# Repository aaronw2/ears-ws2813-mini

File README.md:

# ears-ws2813-mini
New flex board LED project using ws2812-minis instead of sk6812-3535s. Hopefully this will be less sensitive to heat.

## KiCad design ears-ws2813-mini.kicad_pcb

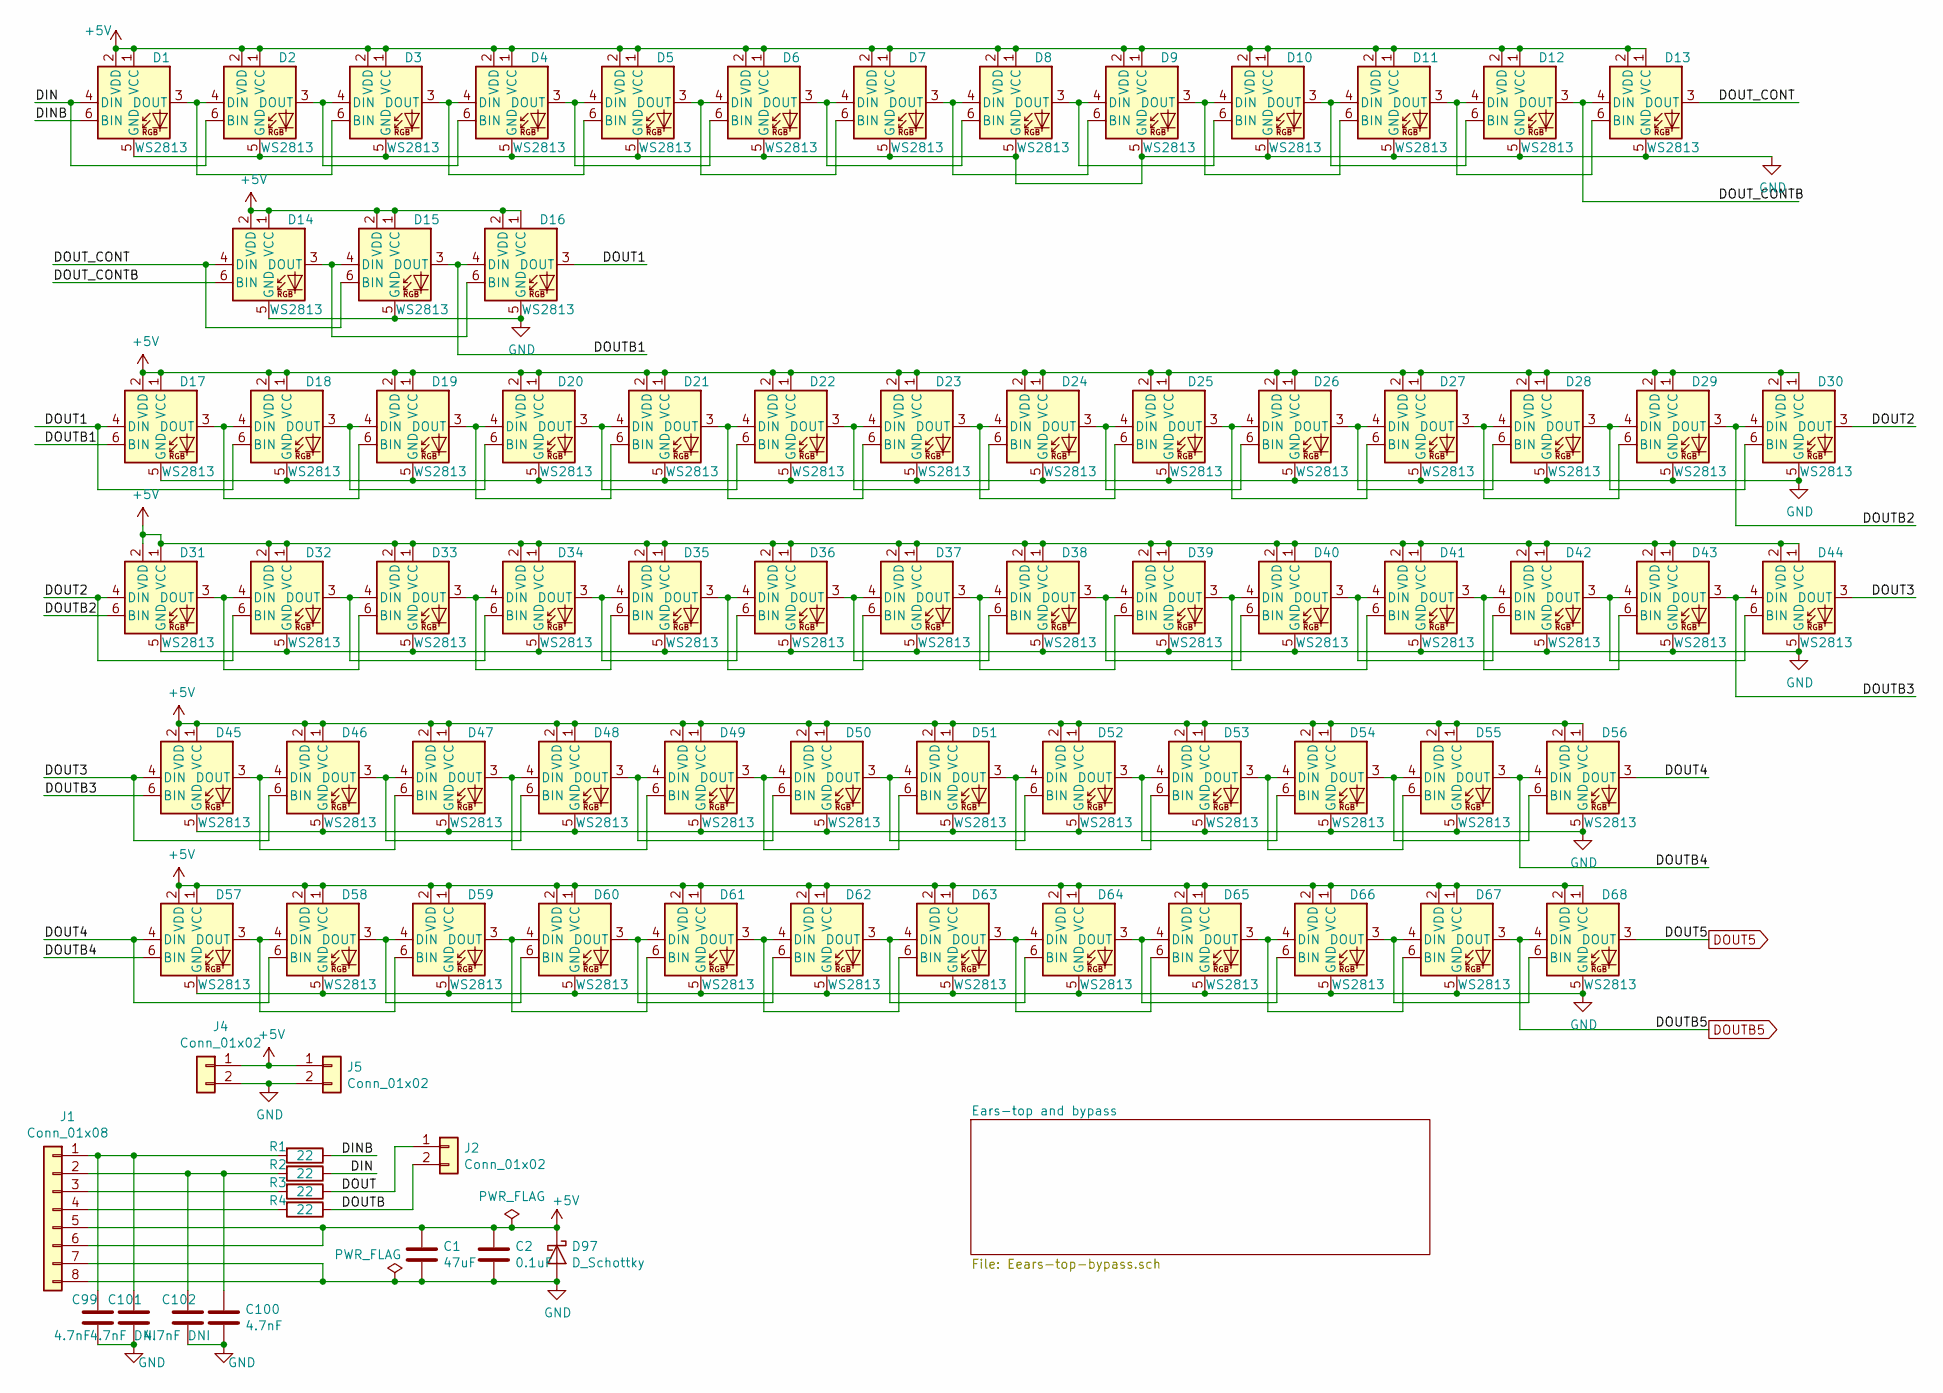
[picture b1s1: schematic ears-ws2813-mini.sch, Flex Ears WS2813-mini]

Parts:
C1: 47uF; C_1210_3225Metric
C2: 0.1uF; C_0603_1608Metric; MPN CL10B104KO8WPNC
C99, C100: 4.7nF; C_0603_1608Metric; MPN CL10B104KO8WPNC
C101, C102: 4.7nF DNI; C_0603_1608Metric; MPN CL10B104KO8WPNC
D1, D2, D3, D4, D5, D6, D7, D8, D9, D10, D11, D12, D13, D14, D15, D16, D17, D18, D19, D20, D21, D22, D23, D24, D25, D26, D27, D28, D29, D30, D31, D32, D33, D34, D35, D36, D37, D38, D39, D40, D41, D42, D43, D44, D45, D46, D47, D48, D49, D50, D51, D52, D53, D54, D55, D56, D57, D58, D59, D60, D61, D62, D63, D64, D65, D66, D67, D68: WS2813; LED_WS2813-MINI-2; MPN WS2813B-Mini
D97: D_Schottky; D_2010_5025Metric; MPN ACDBAT3100-HF
J1: Conn_01x08; PinHeader_1x08_P2.54mm_Vertical
J2, J4, J5: Conn_01x02; PinHeader_1x02_P2.54mm_Vertical
R1, R2, R3, R4: 22; R_0603_1608Metric

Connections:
+5V: C1.1, C2.1, D1.1 (VCC), D1.2 (VDD), D2.1 (VCC), D2.2 (VDD), D3.1 (VCC), D3.2 (VDD), D4.1 (VCC), D4.2 (VDD), D5.1 (VCC), D5.2 (VDD), D6.1 (VCC), D6.2 (VDD), D7.1 (VCC), D7.2 (VDD), D8.1 (VCC), D8.2 (VDD), D9.1 (VCC), D9.2 (VDD), D10.1 (VCC), D10.2 (VDD), D11.1 (VCC), D11.2 (VDD), D12.1 (VCC), D12.2 (VDD), D13.1 (VCC), D13.2 (VDD), D14.1 (VCC), D14.2 (VDD), D15.1 (VCC), D15.2 (VDD), D16.1 (VCC), D16.2 (VDD), D17.1 (VCC), D17.2 (VDD), D18.1 (VCC), D18.2 (VDD), D19.1 (VCC), D19.2 (VDD), D20.1 (VCC), D20.2 (VDD), D21.1 (VCC), D21.2 (VDD), D22.1 (VCC), D22.2 (VDD), D23.1 (VCC), D23.2 (VDD), D24.1 (VCC), D24.2 (VDD), D25.1 (VCC), D25.2 (VDD), D26.1 (VCC), D26.2 (VDD), D27.1 (VCC), D27.2 (VDD), D28.1 (VCC), D28.2 (VDD), D29.1 (VCC), D29.2 (VDD), D30.1 (VCC), D30.2 (VDD), D31.1 (VCC), D31.2 (VDD), D32.1 (VCC), D32.2 (VDD), D33.1 (VCC), D33.2 (VDD), D34.1 (VCC), D34.2 (VDD), D35.1 (VCC), D35.2 (VDD), D36.1 (VCC), D36.2 (VDD), D37.1 (VCC), D37.2 (VDD), D38.1 (VCC), D38.2 (VDD), D39.1 (VCC), D39.2 (VDD), D40.1 (VCC), D40.2 (VDD), D41.1 (VCC), D41.2 (VDD), D42.1 (VCC), D42.2 (VDD), D43.1 (VCC), D43.2 (VDD), D44.1 (VCC), D44.2 (VDD), D45.1 (VCC), D45.2 (VDD), D46.1 (VCC), D46.2 (VDD), D47.1 (VCC), D47.2 (VDD), D48.1 (VCC), D48.2 (VDD), D49.1 (VCC), D49.2 (VDD), D50.1 (VCC), D50.2 (VDD), D51.1 (VCC), D51.2 (VDD), D52.1 (VCC), D52.2 (VDD), D53.1 (VCC), D53.2 (VDD), D54.1 (VCC), D54.2 (VDD), D55.1 (VCC), D55.2 (VDD), D56.1 (VCC), D56.2 (VDD), D57.1 (VCC), D57.2 (VDD), D58.1 (VCC), D58.2 (VDD), D59.1 (VCC), D59.2 (VDD), D60.1 (VCC), D60.2 (VDD), D61.1 (VCC), D61.2 (VDD), D62.1 (VCC), D62.2 (VDD), D63.1 (VCC), D63.2 (VDD), D64.1 (VCC), D64.2 (VDD), D65.1 (VCC), D65.2 (VDD), D66.1 (VCC), D66.2 (VDD), D67.1 (VCC), D67.2 (VDD), D68.1 (VCC), D68.2 (VDD), D97.1 (K), J1.5, J1.6, J4.1, J5.1; also elsewhere on the board
/DIN: D1.4 (DIN), D2.6 (BIN), R2.1
/DINB: D1.6 (BIN), R1.1
/DOUT: J2.1, R3.1
/DOUT1: D16.3 (DOUT), D17.4 (DIN), D18.6 (BIN)
/DOUT2: D30.3 (DOUT), D31.4 (DIN), D32.6 (BIN)
/DOUT3: D44.3 (DOUT), D45.4 (DIN), D46.6 (BIN)
/DOUT4: D56.3 (DOUT), D57.4 (DIN), D58.6 (BIN)
/DOUTB: J2.2, R4.1
/DOUTB1: D15.3 (DOUT), D16.4 (DIN), D17.6 (BIN)
/DOUTB2: D29.3 (DOUT), D30.4 (DIN), D31.6 (BIN)
/DOUTB3: D43.3 (DOUT), D44.4 (DIN), D45.6 (BIN)
/DOUTB4: D55.3 (DOUT), D56.4 (DIN), D57.6 (BIN)
/DOUT_CONT: D13.3 (DOUT), D14.4 (DIN), D15.6 (BIN)
/DOUT_CONTB: D12.3 (DOUT), D13.4 (DIN), D14.6 (BIN)
DOUT5: D68.3 (DOUT); also elsewhere on the board
DOUTB5: D67.3 (DOUT), D68.4 (DIN); also elsewhere on the board
GND: C1.2, C2.2, C99.2, C100.2, C101.2, C102.2, D1.5 (GND), D2.5 (GND), D3.5 (GND), D4.5 (GND), D5.5 (GND), D6.5 (GND), D7.5 (GND), D8.5 (GND), D9.5 (GND), D10.5 (GND), D11.5 (GND), D12.5 (GND), D13.5 (GND), D14.5 (GND), D15.5 (GND), D16.5 (GND), D17.5 (GND), D18.5 (GND), D19.5 (GND), D20.5 (GND), D21.5 (GND), D22.5 (GND), D23.5 (GND), D24.5 (GND), D25.5 (GND), D26.5 (GND), D27.5 (GND), D28.5 (GND), D29.5 (GND), D30.5 (GND), D31.5 (GND), D32.5 (GND), D33.5 (GND), D34.5 (GND), D35.5 (GND), D36.5 (GND), D37.5 (GND), D38.5 (GND), D39.5 (GND), D40.5 (GND), D41.5 (GND), D42.5 (GND), D43.5 (GND), D44.5 (GND), D45.5 (GND), D46.5 (GND), D47.5 (GND), D48.5 (GND), D49.5 (GND), D50.5 (GND), D51.5 (GND), D52.5 (GND), D53.5 (GND), D54.5 (GND), D55.5 (GND), D56.5 (GND), D57.5 (GND), D58.5 (GND), D59.5 (GND), D60.5 (GND), D61.5 (GND), D62.5 (GND), D63.5 (GND), D64.5 (GND), D65.5 (GND), D66.5 (GND), D67.5 (GND), D68.5 (GND), D97.2 (A), J1.7, J1.8, J4.2, J5.2; also elsewhere on the board
unnamed: C100.1, C102.1, J1.2, R2.2
unnamed: C99.1, C101.1, J1.1, R1.2
unnamed: D1.3 (DOUT), D2.4 (DIN), D3.6 (BIN)
unnamed: D2.3 (DOUT), D3.4 (DIN), D4.6 (BIN)
unnamed: D3.3 (DOUT), D4.4 (DIN), D5.6 (BIN)
unnamed: D4.3 (DOUT), D5.4 (DIN), D6.6 (BIN)
unnamed: D5.3 (DOUT), D6.4 (DIN), D7.6 (BIN)
unnamed: D6.3 (DOUT), D7.4 (DIN), D8.6 (BIN)
unnamed: D7.3 (DOUT), D8.4 (DIN), D9.6 (BIN)
unnamed: D10.3 (DOUT), D11.4 (DIN), D12.6 (BIN)
unnamed: D9.3 (DOUT), D10.4 (DIN), D11.6 (BIN)
unnamed: D8.3 (DOUT), D9.4 (DIN), D10.6 (BIN)
unnamed: D11.3 (DOUT), D12.4 (DIN), D13.6 (BIN)
unnamed: D14.3 (DOUT), D15.4 (DIN), D16.6 (BIN)
unnamed: D17.3 (DOUT), D18.4 (DIN), D19.6 (BIN)
unnamed: D18.3 (DOUT), D19.4 (DIN), D20.6 (BIN)
unnamed: D19.3 (DOUT), D20.4 (DIN), D21.6 (BIN)
unnamed: D20.3 (DOUT), D21.4 (DIN), D22.6 (BIN)
unnamed: D21.3 (DOUT), D22.4 (DIN), D23.6 (BIN)
unnamed: D22.3 (DOUT), D23.4 (DIN), D24.6 (BIN)
unnamed: D23.3 (DOUT), D24.4 (DIN), D25.6 (BIN)
unnamed: D24.3 (DOUT), D25.4 (DIN), D26.6 (BIN)
unnamed: D25.3 (DOUT), D26.4 (DIN), D27.6 (BIN)
unnamed: D26.3 (DOUT), D27.4 (DIN), D28.6 (BIN)
unnamed: D27.3 (DOUT), D28.4 (DIN), D29.6 (BIN)
unnamed: D28.3 (DOUT), D29.4 (DIN), D30.6 (BIN)
unnamed: D31.3 (DOUT), D32.4 (DIN), D33.6 (BIN)
unnamed: D32.3 (DOUT), D33.4 (DIN), D34.6 (BIN)
unnamed: D33.3 (DOUT), D34.4 (DIN), D35.6 (BIN)
unnamed: D34.3 (DOUT), D35.4 (DIN), D36.6 (BIN)
unnamed: D35.3 (DOUT), D36.4 (DIN), D37.6 (BIN)
unnamed: D36.3 (DOUT), D37.4 (DIN), D38.6 (BIN)
unnamed: D37.3 (DOUT), D38.4 (DIN), D39.6 (BIN)
unnamed: D38.3 (DOUT), D39.4 (DIN), D40.6 (BIN)
unnamed: D39.3 (DOUT), D40.4 (DIN), D41.6 (BIN)
unnamed: D40.3 (DOUT), D41.4 (DIN), D42.6 (BIN)
unnamed: D41.3 (DOUT), D42.4 (DIN), D43.6 (BIN)
unnamed: D42.3 (DOUT), D43.4 (DIN), D44.6 (BIN)
unnamed: D45.3 (DOUT), D46.4 (DIN), D47.6 (BIN)
unnamed: D46.3 (DOUT), D47.4 (DIN), D48.6 (BIN)
unnamed: D47.3 (DOUT), D48.4 (DIN), D49.6 (BIN)
unnamed: D48.3 (DOUT), D49.4 (DIN), D50.6 (BIN)
unnamed: D49.3 (DOUT), D50.4 (DIN), D51.6 (BIN)
unnamed: D50.3 (DOUT), D51.4 (DIN), D52.6 (BIN)
unnamed: D51.3 (DOUT), D52.4 (DIN), D53.6 (BIN)
unnamed: D52.3 (DOUT), D53.4 (DIN), D54.6 (BIN)
unnamed: D53.3 (DOUT), D54.4 (DIN), D55.6 (BIN)
unnamed: D54.3 (DOUT), D55.4 (DIN), D56.6 (BIN)
unnamed: D57.3 (DOUT), D58.4 (DIN), D59.6 (BIN)
unnamed: D58.3 (DOUT), D59.4 (DIN), D60.6 (BIN)
unnamed: D59.3 (DOUT), D60.4 (DIN), D61.6 (BIN)
unnamed: D60.3 (DOUT), D61.4 (DIN), D62.6 (BIN)
unnamed: D61.3 (DOUT), D62.4 (DIN), D63.6 (BIN)
unnamed: D62.3 (DOUT), D63.4 (DIN), D64.6 (BIN)
unnamed: D63.3 (DOUT), D64.4 (DIN), D65.6 (BIN)
unnamed: D64.3 (DOUT), D65.4 (DIN), D66.6 (BIN)
unnamed: D65.3 (DOUT), D66.4 (DIN), D67.6 (BIN)
unnamed: D66.3 (DOUT), D67.4 (DIN), D68.6 (BIN)
unnamed: J1.3, R3.2
unnamed: J1.4, R4.2

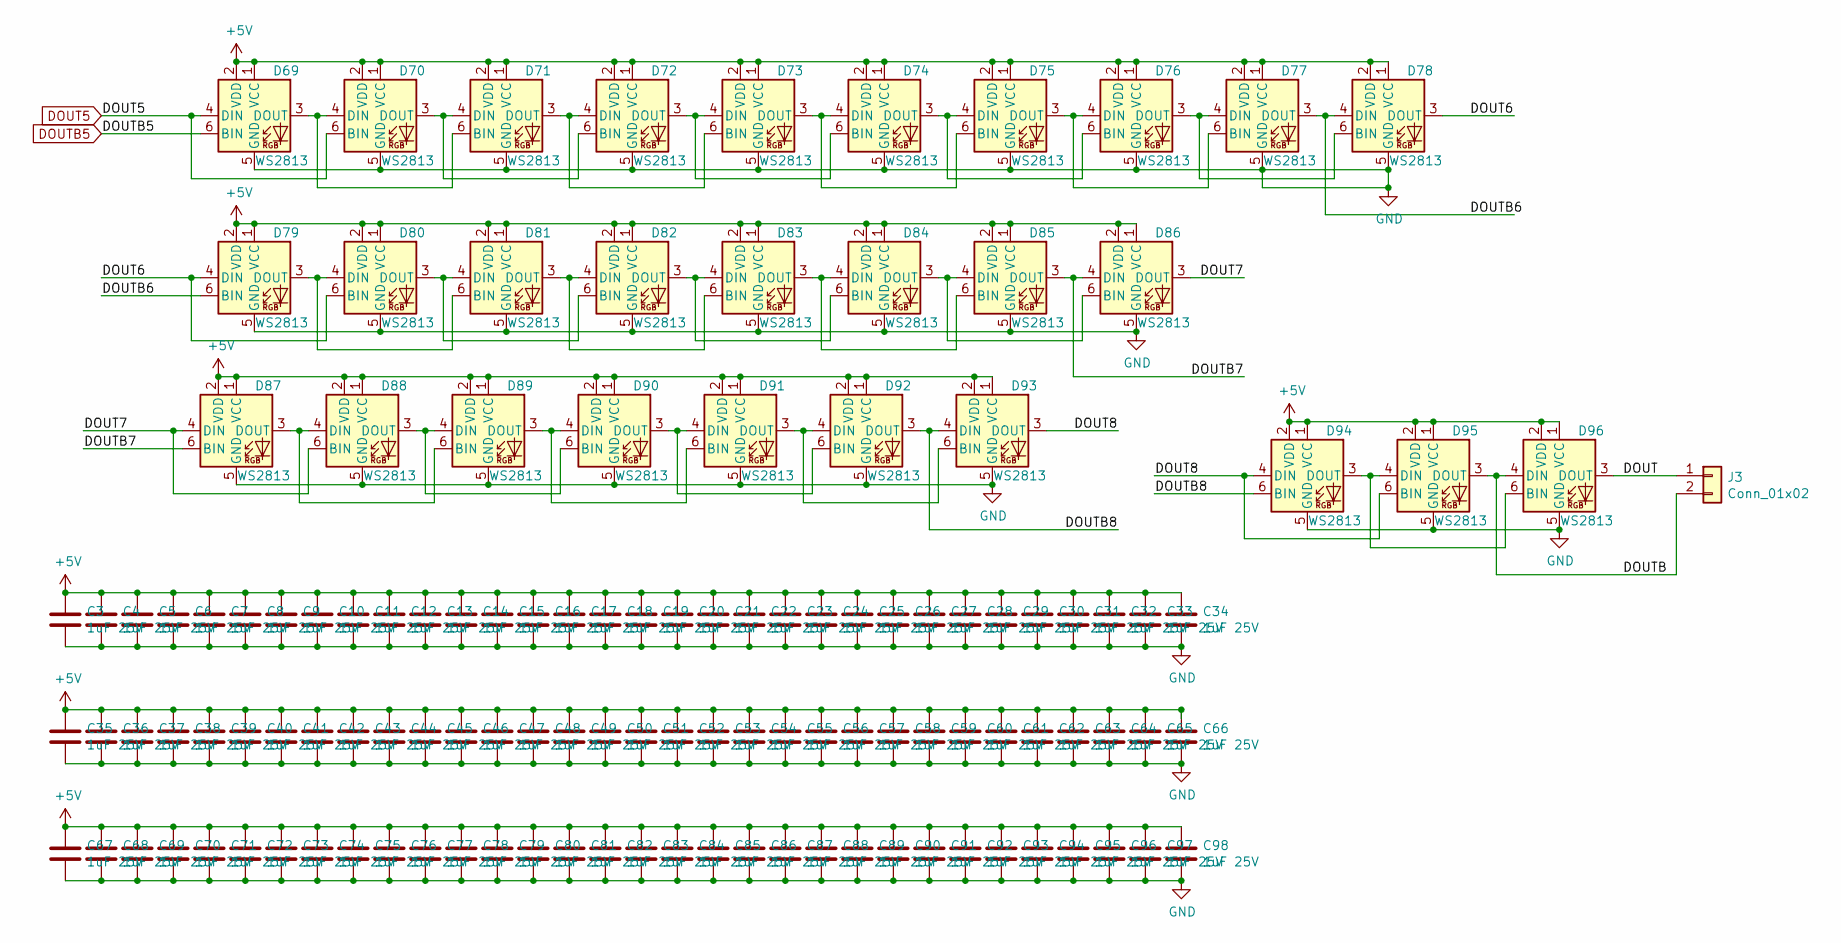
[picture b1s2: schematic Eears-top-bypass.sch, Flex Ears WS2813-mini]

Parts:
C3, C4, C5, C6, C7, C8, C9, C10, C11, C12, C13, C14, C15, C16, C17, C18, C19, C20, C21, C22, C23, C24, C25, C26, C27, C28, C29, C30, C31, C32, C33, C34, C35, C36, C37, C38, C39, C40, C41, C42, C43, C44, C45, C46, C47, C48, C49, C50, C51, C52, C53, C54, C55, C56, C57, C58, C59, C60, C61, C62, C63, C64, C65, C66, C67, C68, C69, C70, C71, C72, C73, C74, C75, C76, C77, C78, C79, C80, C81, C82, C83, C84, C85, C86, C87, C88, C89, C90, C91, C92, C93, C94, C95, C96, C97, C98: 1uF 25V; C_0603_1608Metric; MPN CL10B105KA8NNNC
D69, D70, D71, D72, D73, D74, D75, D76, D77, D78, D79, D80, D81, D82, D83, D84, D85, D86, D87, D88, D89, D90, D91, D92, D93, D94, D95, D96: WS2813; LED_WS2813-MINI; MPN WS2813B-Mini
J3: Conn_01x02; PinHeader_1x02_P2.54mm_Vertical

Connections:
+5V: C3.1, C4.1, C5.1, C6.1, C7.1, C8.1, C9.1, C10.1, C11.1, C12.1, C13.1, C14.1, C15.1, C16.1, C17.1, C18.1, C19.1, C20.1, C21.1, C22.1, C23.1, C24.1, C25.1, C26.1, C27.1, C28.1, C29.1, C30.1, C31.1, C32.1, C33.1, C34.1, C35.1, C36.1, C37.1, C38.1, C39.1, C40.1, C41.1, C42.1, C43.1, C44.1, C45.1, C46.1, C47.1, C48.1, C49.1, C50.1, C51.1, C52.1, C53.1, C54.1, C55.1, C56.1, C57.1, C58.1, C59.1, C60.1, C61.1, C62.1, C63.1, C64.1, C65.1, C66.1, C67.1, C68.1, C69.1, C70.1, C71.1, C72.1, C73.1, C74.1, C75.1, C76.1, C77.1, C78.1, C79.1, C80.1, C81.1, C82.1, C83.1, C84.1, C85.1, C86.1, C87.1, C88.1, C89.1, C90.1, C91.1, C92.1, C93.1, C94.1, C95.1, C96.1, C97.1, C98.1, D69.1 (VCC), D69.2 (VDD), D70.1 (VCC), D70.2 (VDD), D71.1 (VCC), D71.2 (VDD), D72.1 (VCC), D72.2 (VDD), D73.1 (VCC), D73.2 (VDD), D74.1 (VCC), D74.2 (VDD), D75.1 (VCC), D75.2 (VDD), D76.1 (VCC), D76.2 (VDD), D77.1 (VCC), D77.2 (VDD), D78.1 (VCC), D78.2 (VDD), D79.1 (VCC), D79.2 (VDD), D80.1 (VCC), D80.2 (VDD), D81.1 (VCC), D81.2 (VDD), D82.1 (VCC), D82.2 (VDD), D83.1 (VCC), D83.2 (VDD), D84.1 (VCC), D84.2 (VDD), D85.1 (VCC), D85.2 (VDD), D86.1 (VCC), D86.2 (VDD), D87.1 (VCC), D87.2 (VDD), D88.1 (VCC), D88.2 (VDD), D89.1 (VCC), D89.2 (VDD), D90.1 (VCC), D90.2 (VDD), D91.1 (VCC), D91.2 (VDD), D92.1 (VCC), D92.2 (VDD), D93.1 (VCC), D93.2 (VDD), D94.1 (VCC), D94.2 (VDD), D95.1 (VCC), D95.2 (VDD), D96.1 (VCC), D96.2 (VDD); also elsewhere on the board
/Ears-top and bypass/DOUT: D96.3 (DOUT), J3.1
/Ears-top and bypass/DOUT6: D78.3 (DOUT), D79.4 (DIN), D80.6 (BIN)
/Ears-top and bypass/DOUT7: D86.3 (DOUT), D87.4 (DIN), D88.6 (BIN)
/Ears-top and bypass/DOUT8: D93.3 (DOUT), D94.4 (DIN), D95.6 (BIN)
/Ears-top and bypass/DOUTB: D95.3 (DOUT), D96.4 (DIN), J3.2
/Ears-top and bypass/DOUTB6: D77.3 (DOUT), D78.4 (DIN), D79.6 (BIN)
/Ears-top and bypass/DOUTB7: D85.3 (DOUT), D86.4 (DIN), D87.6 (BIN)
/Ears-top and bypass/DOUTB8: D92.3 (DOUT), D93.4 (DIN), D94.6 (BIN)
DOUT5: D69.4 (DIN), D70.6 (BIN); also elsewhere on the board
DOUTB5: D69.6 (BIN); also elsewhere on the board
GND: C3.2, C4.2, C5.2, C6.2, C7.2, C8.2, C9.2, C10.2, C11.2, C12.2, C13.2, C14.2, C15.2, C16.2, C17.2, C18.2, C19.2, C20.2, C21.2, C22.2, C23.2, C24.2, C25.2, C26.2, C27.2, C28.2, C29.2, C30.2, C31.2, C32.2, C33.2, C34.2, C35.2, C36.2, C37.2, C38.2, C39.2, C40.2, C41.2, C42.2, C43.2, C44.2, C45.2, C46.2, C47.2, C48.2, C49.2, C50.2, C51.2, C52.2, C53.2, C54.2, C55.2, C56.2, C57.2, C58.2, C59.2, C60.2, C61.2, C62.2, C63.2, C64.2, C65.2, C66.2, C67.2, C68.2, C69.2, C70.2, C71.2, C72.2, C73.2, C74.2, C75.2, C76.2, C77.2, C78.2, C79.2, C80.2, C81.2, C82.2, C83.2, C84.2, C85.2, C86.2, C87.2, C88.2, C89.2, C90.2, C91.2, C92.2, C93.2, C94.2, C95.2, C96.2, C97.2, C98.2, D69.5 (GND), D70.5 (GND), D71.5 (GND), D72.5 (GND), D73.5 (GND), D74.5 (GND), D75.5 (GND), D76.5 (GND), D77.5 (GND), D78.5 (GND), D79.5 (GND), D80.5 (GND), D81.5 (GND), D82.5 (GND), D83.5 (GND), D84.5 (GND), D85.5 (GND), D86.5 (GND), D87.5 (GND), D88.5 (GND), D89.5 (GND), D90.5 (GND), D91.5 (GND), D92.5 (GND), D93.5 (GND), D94.5 (GND), D95.5 (GND), D96.5 (GND); also elsewhere on the board
unnamed: D69.3 (DOUT), D70.4 (DIN), D71.6 (BIN)
unnamed: D70.3 (DOUT), D71.4 (DIN), D72.6 (BIN)
unnamed: D71.3 (DOUT), D72.4 (DIN), D73.6 (BIN)
unnamed: D72.3 (DOUT), D73.4 (DIN), D74.6 (BIN)
unnamed: D73.3 (DOUT), D74.4 (DIN), D75.6 (BIN)
unnamed: D74.3 (DOUT), D75.4 (DIN), D76.6 (BIN)
unnamed: D75.3 (DOUT), D76.4 (DIN), D77.6 (BIN)
unnamed: D76.3 (DOUT), D77.4 (DIN), D78.6 (BIN)
unnamed: D79.3 (DOUT), D80.4 (DIN), D81.6 (BIN)
unnamed: D80.3 (DOUT), D81.4 (DIN), D82.6 (BIN)
unnamed: D81.3 (DOUT), D82.4 (DIN), D83.6 (BIN)
unnamed: D82.3 (DOUT), D83.4 (DIN), D84.6 (BIN)
unnamed: D83.3 (DOUT), D84.4 (DIN), D85.6 (BIN)
unnamed: D84.3 (DOUT), D85.4 (DIN), D86.6 (BIN)
unnamed: D87.3 (DOUT), D88.4 (DIN), D89.6 (BIN)
unnamed: D88.3 (DOUT), D89.4 (DIN), D90.6 (BIN)
unnamed: D89.3 (DOUT), D90.4 (DIN), D91.6 (BIN)
unnamed: D90.3 (DOUT), D91.4 (DIN), D92.6 (BIN)
unnamed: D91.3 (DOUT), D92.4 (DIN), D93.6 (BIN)
unnamed: D94.3 (DOUT), D95.4 (DIN), D96.6 (BIN)

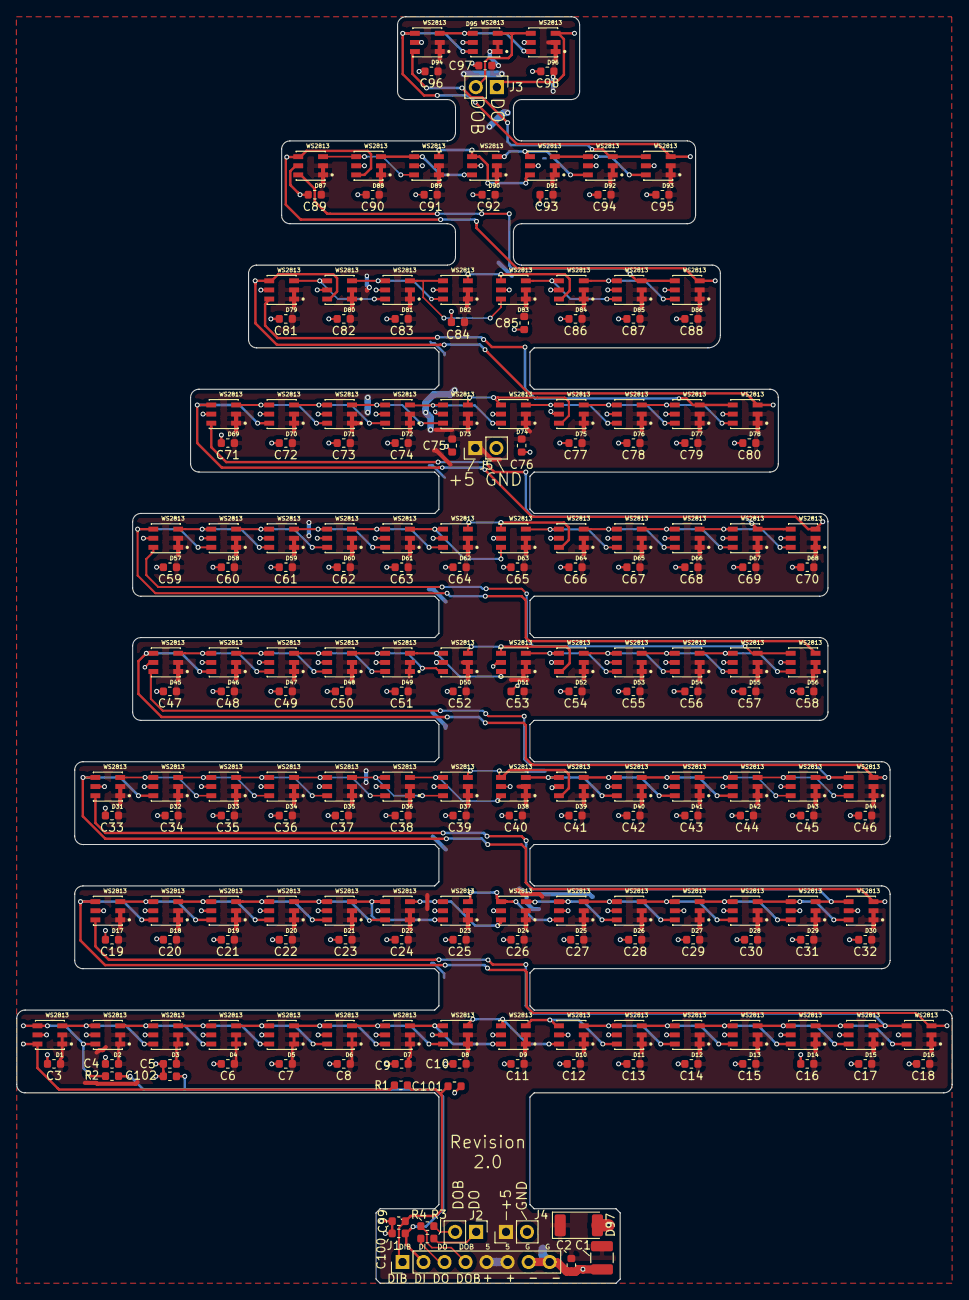
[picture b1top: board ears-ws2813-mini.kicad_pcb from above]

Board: 2 copper layers, 113.0 x 153.0 mm, 208 parts (0 on the bottom side), 106 nets.

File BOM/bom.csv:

Refs,Value,Footprint,Quantity,MFR,MPN,SPR,SPN
C2,0.1uF,Capacitor_SMD:C_0603_1608Metric,1,Samsung,CL10B104KO8WPNC,Digikey,1276-6582-1-ND
C3;C4;C5;C6;C7;C8;C9;C10;C11;C12;C13;C14;C15;C16;C17;C18;C19;C20;C21;C22;C23;C24;C25;C26;C27;C28;C29;C30;C31;C32;C33;C34;C35;C36;C37;C38;C39;C40;C41;C42;C43;C44;C45;C46;C47;C48;C49;C50;C51;C52;C53;C54;C55;C56;C57;C58;C59;C60;C61;C62;C63;C64;C65;C66;C67;C68;C69;C70;C71;C72;C73;C74;C75;C76;C77;C78;C79;C80;C81;C82;C83;C84;C85;C86;C87;C88;C89;C90;C91;C92;C93;C94;C95;C96;C97;C98,1uF 25V,Capacitor_SMD:C_0603_1608Metric,96,Samsung,CL10B105KA8NNNC,Digikey,1276-1184-1-ND
C99;C100,4.7nF,Capacitor_SMD:C_0603_1608Metric,2,Samsung,CL10B104KO8WPNC,Digikey,1276-6582-1-ND
C101;C102,4.7nF DNI,Capacitor_SMD:C_0603_1608Metric,2,Samsung,CL10B104KO8WPNC,Digikey,1276-6582-1-ND
C1,47uF,Capacitor_SMD:C_1210_3225Metric,1,-,-,-,-
J3;J2;J5;J4,Conn_01x02,Connector_PinHeader_2.54mm:PinHeader_1x02_P2.54mm_Vertical,4,-,-,-,-
J1,Conn_01x08,Connector_PinHeader_2.54mm:PinHeader_1x08_P2.54mm_Vertical,1,-,-,-,-
D97,D_Schottky,Diode_SMD:D_2010_5025Metric,1,Comchip Technology,ACDBAT3100-HF,Digikey,641-1607-1-ND
D87;D88;D89;D90;D91;D92;D93;D94;D95;D96;D69;D70;D71;D72;D73;D74;D75;D76;D77;D78;D79;D80;D81;D82;D83;D84;D85;D86;D1;D2;D3;D4;D5;D6;D7;D8;D9;D10;D11;D12;D13;D14;D45;D46;D47;D48;D49;D50;D51;D52;D53;D54;D55;D56;D57;D58;D59;D60;D61;D62;D63;D64;D65;D66;D67;D68;D15;D16;D17;D18;D19;D20;D21;D22;D23;D24;D25;D26;D27;D28;D29;D30;D31;D32;D33;D34;D35;D36;D37;D38;D39;D40;D41;D42;D43;D44,WS2813,LED_WS2813-mini:LED_WS2813-MINI-2,96,World Semi,WS2813B-Mini,-,-
R3;R1;R2;R4,22,Resistor_SMD:R_0603_1608Metric,4,-,-,-,-

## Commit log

2019-05-05 Initial checkin. Note that KiCad is generating erroneous DRC errors.
    Also, the PCB editor is not showing anything.
2019-05-23 Cleaned up ears and added protection diode.
    The diode should short things out should power and ground be
    reversed.
    Added new footprint for WS2813B-Minis. Note that this footprint has
    not yet been tested.
2019-11-11 Hopefully this will be revision 2.0
2019-11-14 Changing via size from 0.3 to 0.35mm
2019-12-20 Added more ESD protection and moved a few components.
    Version 2.0

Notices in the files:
Eears-top-bypass.sch:
Copyright © 2019 Aaron Williams
ears-ws2813-mini.kicad_pcb:
Copyrighjt © 2019 by Aaron Williams
Copyright © 2019 by Aaron Williams
